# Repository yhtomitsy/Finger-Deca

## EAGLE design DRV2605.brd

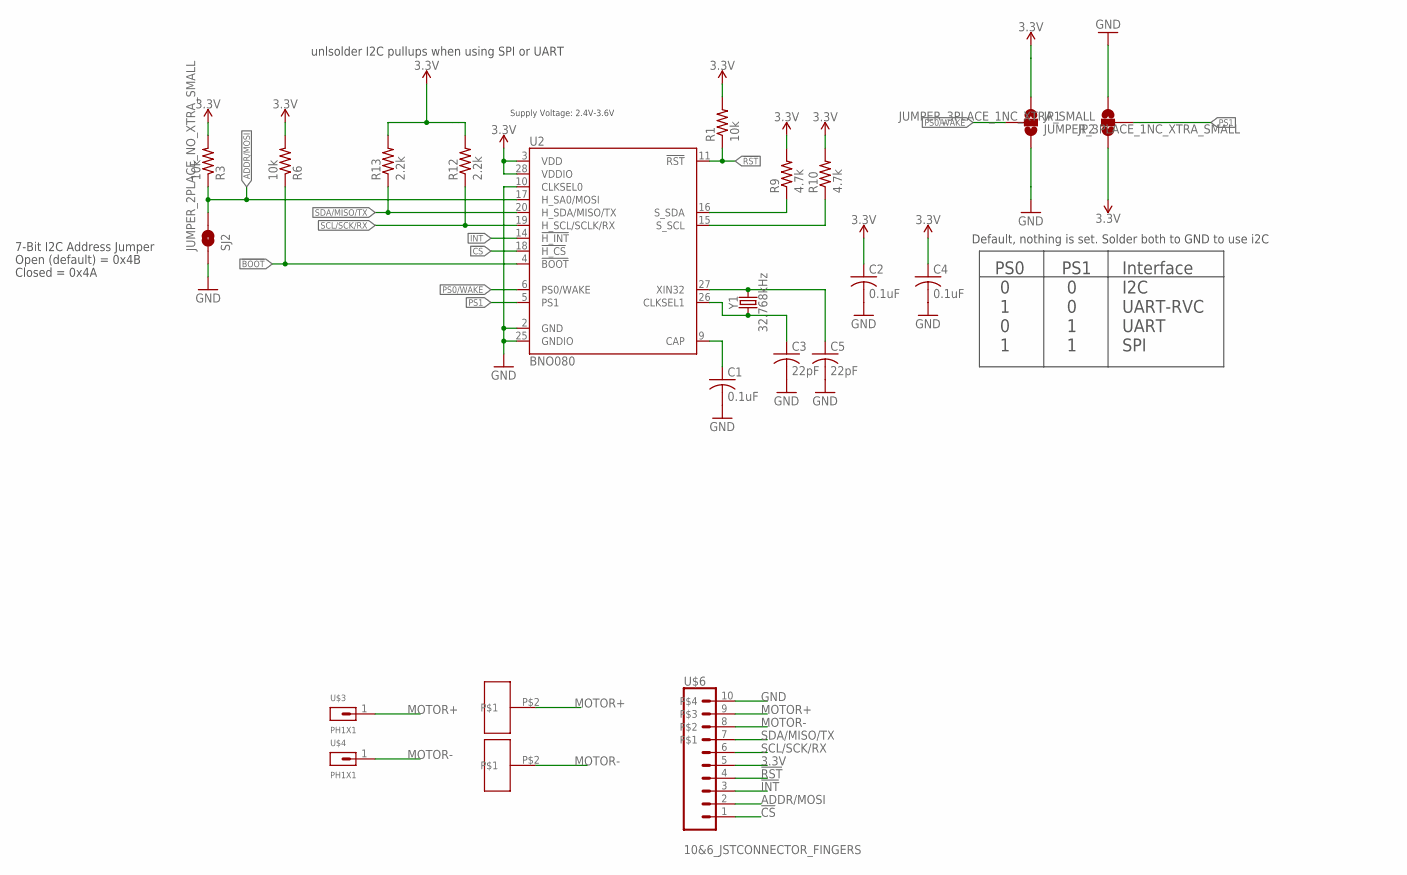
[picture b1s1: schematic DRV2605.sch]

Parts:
C1, C2, C4: 0.1uF; C0402
C3, C5: 22pF; C0402
JP1, JP2: JUMPER_3PLACE_1NC_XTRA_SMALL; XTRA_SMAL_JUMPER_3_1_NC
R1, R3, R6: 10k; R0402
R9, R10: 4.7k; R0402
R12, R13: 2.2k; R0402
SJ2: JUMPER_2PLACE_NO_XTRA_SMALL; XTRA_SMALLJUMPER_NO
U2: BNO080; LGA-28
U$1, U$2: SMD_PIN_1; SMD_PIN
U$3, U$4: PH1X1; PH005-1-1
U$6: 10&6_JSTCONNECTOR_FINGERS; 10&4_HORIZONTAL_JST_CONN
Y1: 32.768kHz; CRYSTAL-SMD-3.2X1.5MM

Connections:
3.3V: C2.1, C4.1, JP1.1, JP2.1, R1.2, R3.2, R6.2, R9.2, R10.2, R12.2, R13.2, U2.3 (VDD), U2.28 (VDDIO), U$6.5
!BOOT: R6.1, U2.4 (!BOOT)
!CS: U2.18 (!H_CS), U$6.1
!INT: U2.14 (!H_INT), U$6.3
!RST: R1.1, U2.11 (!RST), U$6.4
ADDR/MOSI: R3.1, SJ2.2, U2.17 (H_SA0/MOSI), U$6.2
CAP: C1.1, U2.9 (CAP)
GND: C1.2, C2.2, C3.2, C4.2, C5.2, JP1.3, JP2.3, SJ2.1, U2.2 (GND), U2.10 (CLKSEL0), U2.25 (GNDIO), U$6.10
MOTOR+: U$1.P$2, U$3.1, U$6.9
MOTOR-: U$2.P$2, U$4.1, U$6.8
unnamed: C5.1, U2.27 (XIN32), Y1.P$2 (2)
unnamed: C3.1, U2.26 (CLKSEL1), Y1.P$1 (1)
PS0/WAKE: JP1.2, U2.6 (PS0/WAKE)
PS1: JP2.2, U2.5 (PS1)
SCL/SCK/RX: R12.1, U2.19 (H_SCL/SCLK/RX), U$6.6
SDA/MISO/TX: R13.1, U2.20 (H_SDA/MISO/TX), U$6.7
S_SCL: R10.1, U2.15 (S_SCL)
S_SDA: R9.1, U2.16 (S_SDA)

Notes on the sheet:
7-Bit I2C Address Jumper
Closed = 0x4A
Open (default) = 0x4B
PS0 0 1 0 1
PS1 0 0 1 1
Interface I2C UART-RVC UART SPI
Default, nothing is set. Solder both to GND to use i2C
unlsolder I2C pullups when using SPI or UART
Supply Voltage: 2.4V-3.6V

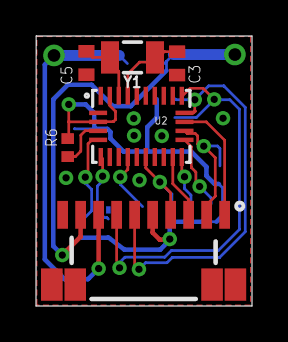
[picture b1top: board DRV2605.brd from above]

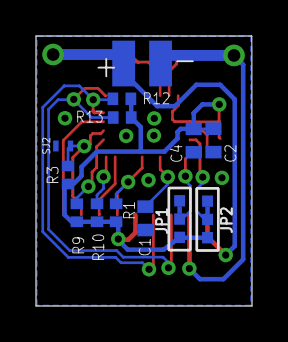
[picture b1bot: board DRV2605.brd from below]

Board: 2 copper layers, 12.0 x 15.0 mm, 22 parts (14 on the bottom side), 18 nets.

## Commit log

2018-10-01 Added my project
2018-10-01 complete No SPI
2018-10-02 SPI connector done
2018-10-02 Complete awaiting DRC
2018-10-02 Complete
2018-10-11 7DRVs ARM done
2018-10-13 USB port added; motor connectors removed
2018-10-13 USB PCB size adjusted
2018-10-14 USB Finger PCB done

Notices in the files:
parts and their libraries:
SparkFun-IC-Special-Function: Licensing: Creative Commons ShareAlike 4.0 International - https://creativecommons.org/licenses/by-sa/4.0
